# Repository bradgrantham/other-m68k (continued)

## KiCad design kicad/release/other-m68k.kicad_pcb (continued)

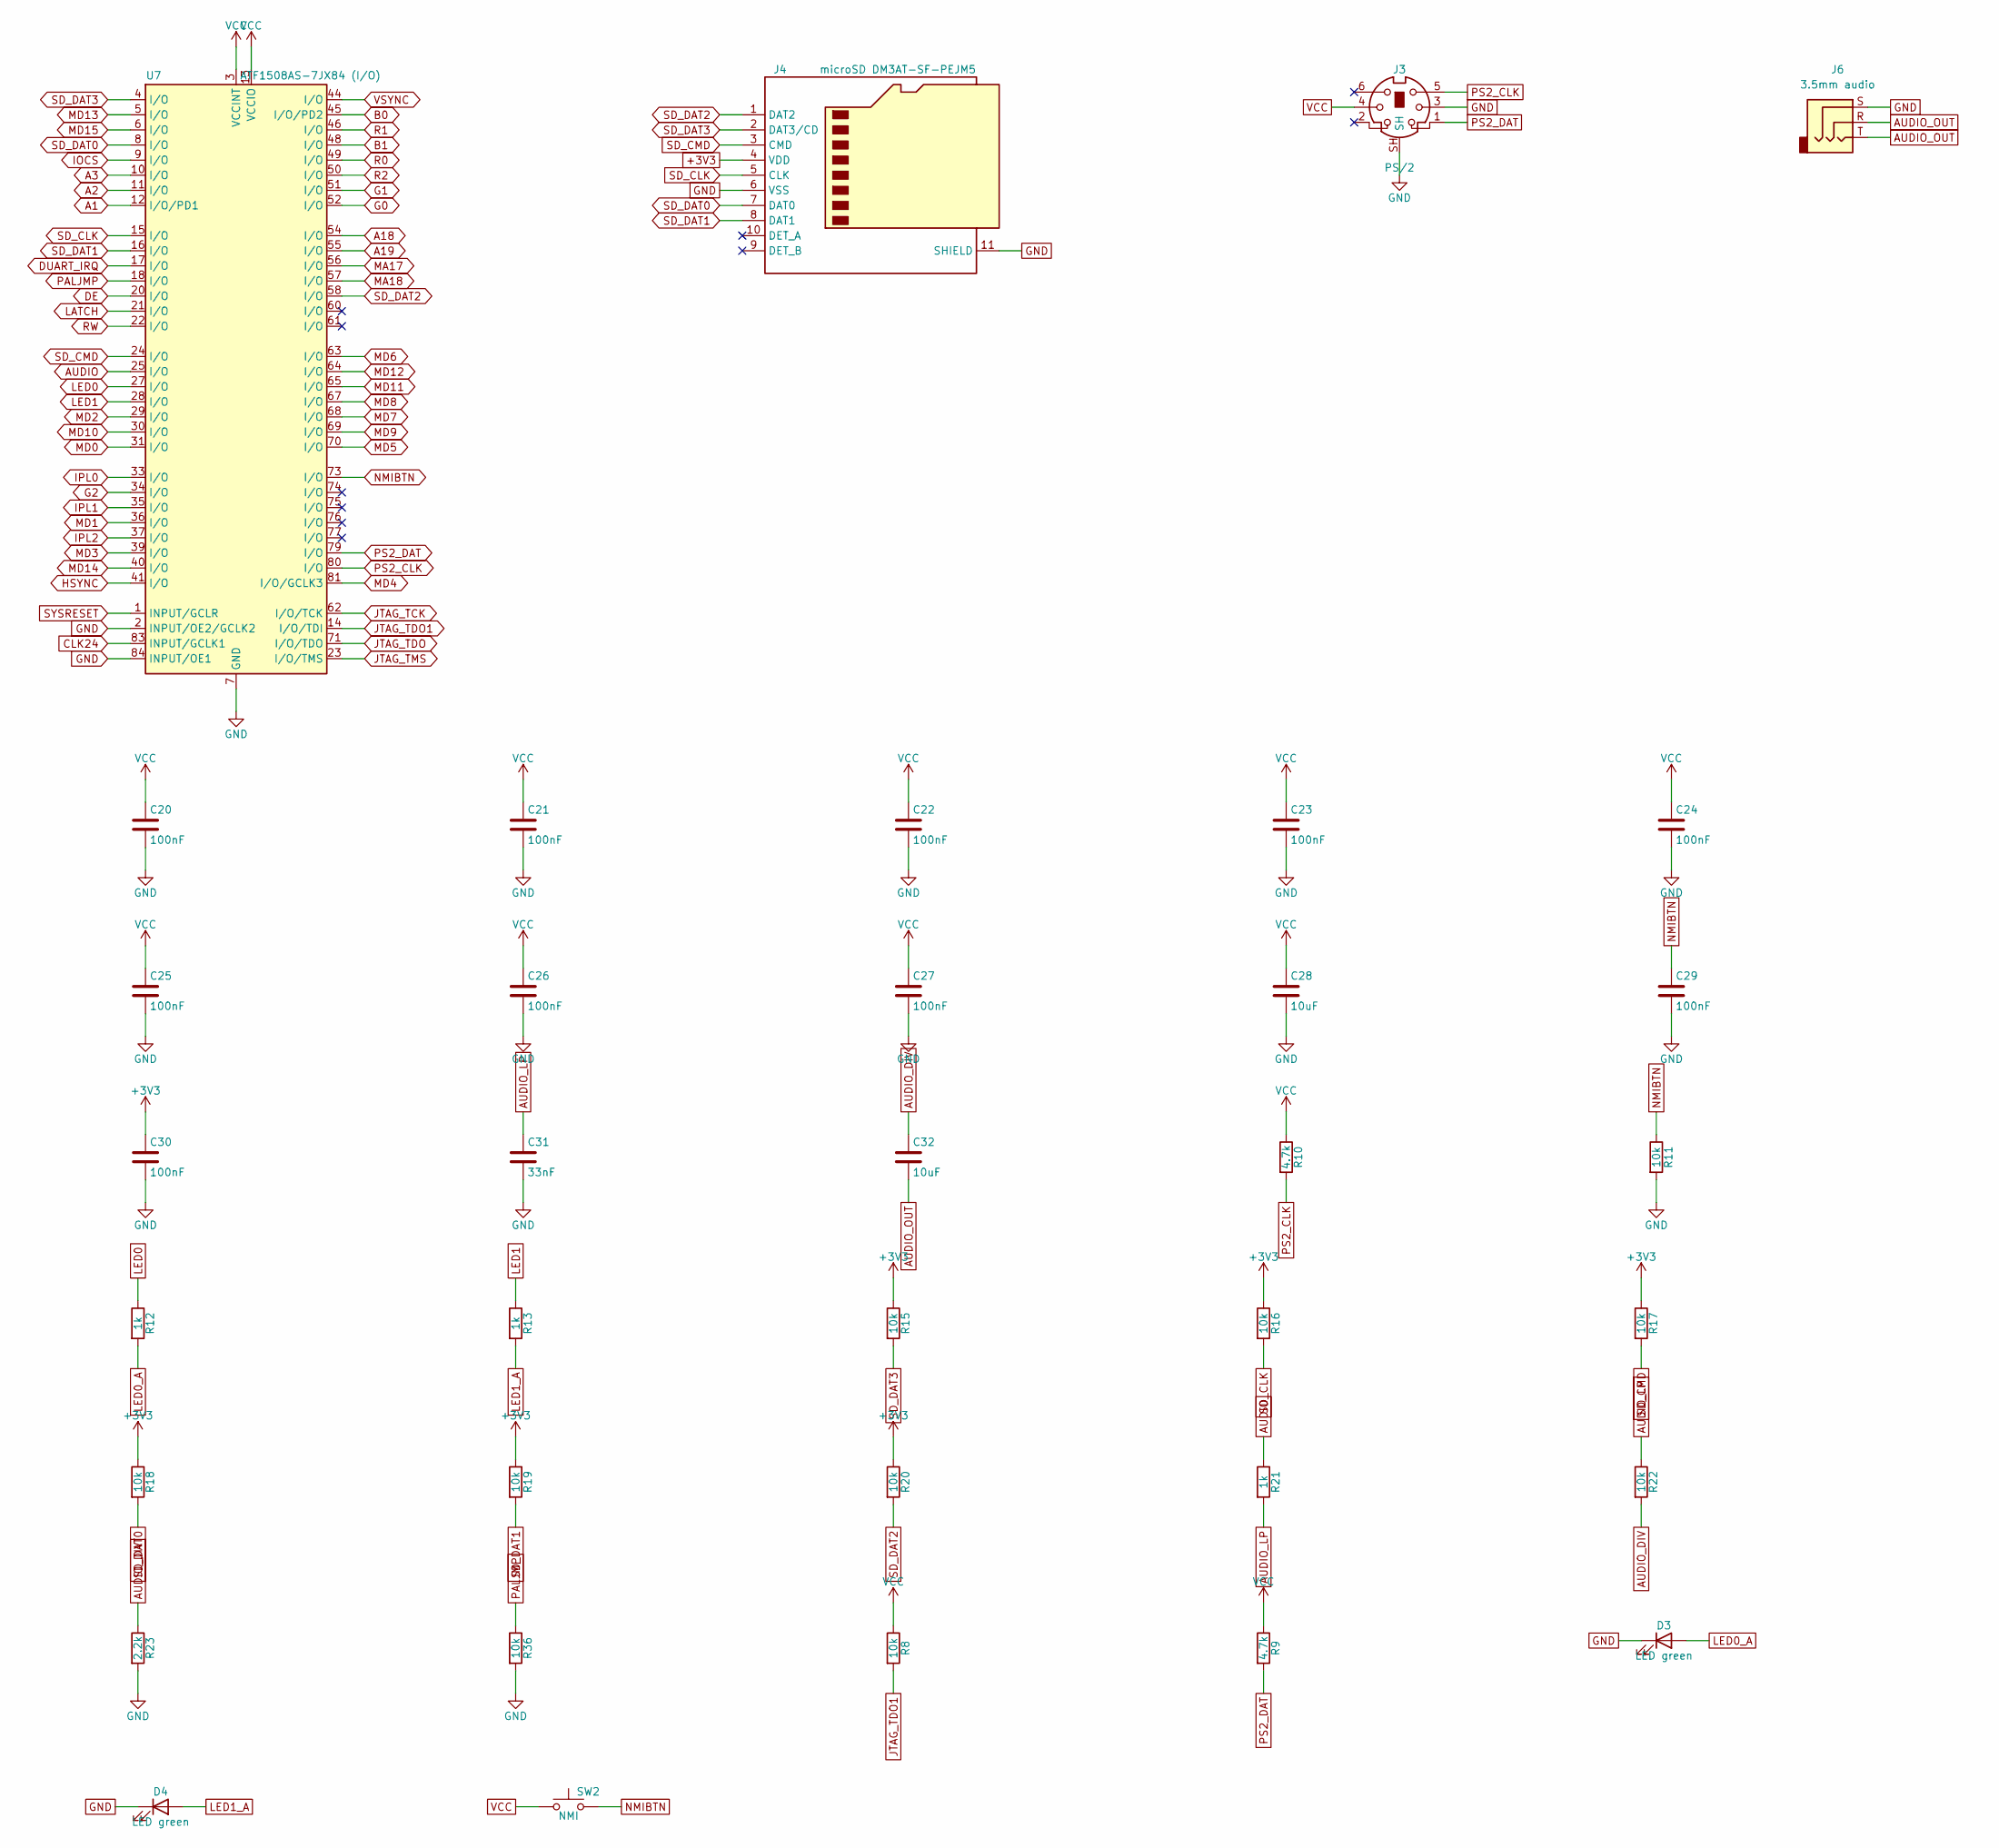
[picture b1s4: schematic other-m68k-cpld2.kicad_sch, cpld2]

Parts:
C20, C21, C22, C23, C24, C25, C26, C27, C29, C30: 100nF; C_0603_1608Metric; MPN CL10B104KB8NNNC; LCSC C1591
C28, C32: 10uF; C_0805_2012Metric; MPN CL21A106KAYNNNE; LCSC C15850
C31: 33nF; C_0603_1608Metric; MPN CL10B333KB8NFNC; LCSC C307488
D3, D4: LED green; LED_0805_2012Metric; MPN LTST-C171GKT
J3: PS/2; MiniDIN-6_CUI_MD-60SM_Horizontal; MPN MD-60SM
J4: microSD DM3AT-SF-PEJM5; microSD_HC_Hirose_DM3AT-SF-PEJM5; MPN DM3AT-SF-PEJM5
J6: 3.5mm audio; Jack_3.5mm_CUI_SJ1-3523N_Horizontal; MPN SJ1-3523N
R8, R11, R15, R16, R17, R18, R19, R20, R22, R36: 10k; R_0603_1608Metric; MPN RC0603FR-0710KL; LCSC C25804
R9, R10: 4.7k; R_0603_1608Metric; MPN RC0603FR-074K7L; LCSC C23162
R12, R13, R21: 1k; R_0603_1608Metric; MPN RC0603FR-071KL; LCSC C21190
R23: 2.2k; R_0603_1608Metric; MPN RC0603FR-072K2L; LCSC C4190
SW2: NMI; SW_PUSH_6mm; MPN B3F-1000
U7: ATF1508AS-7JX84 (I/O); PLCC-84_THT-Socket; MPN ATF1508AS-7JX84

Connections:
+3V3: C30.1, J4.4 (VDD), R15.1, R16.1, R17.1, R18.1, R19.1, R20.1; also elsewhere on the board
A1: U7.12 (I/O/PD1); also elsewhere on the board
A2: U7.11 (I/O); also elsewhere on the board
A3: U7.10 (I/O); also elsewhere on the board
A18: U7.54 (I/O); also elsewhere on the board
A19: U7.55 (I/O); also elsewhere on the board
AUDIO: R21.1, U7.25 (I/O)
AUDIO_DIV: C32.1, R22.2, R23.1
AUDIO_LP: C31.1, R21.2, R22.1
AUDIO_OUT: C32.2, J6.R, J6.T
B0: U7.45 (I/O/PD2); also elsewhere on the board
B1: U7.48 (I/O); also elsewhere on the board
CLK24: U7.83 (INPUT/GCLK1); also elsewhere on the board
DE: U7.20 (I/O); also elsewhere on the board
DUART_IRQ: U7.17 (I/O); also elsewhere on the board
G0: U7.52 (I/O); also elsewhere on the board
G1: U7.51 (I/O); also elsewhere on the board
G2: U7.34 (I/O); also elsewhere on the board
GND: C20.2, C21.2, C22.2, C23.2, C24.2, C25.2, C26.2, C27.2, C28.2, C29.2, C30.2, C31.2, D3.1 (K), D4.1 (K), J3.3, J3.SH, J4.6 (VSS), J4.11 (SHIELD), J6.S, R11.2, R23.2, R36.2, U7.2 (INPUT/OE2/GCLK2), U7.7 (GND), U7.19 (GND), U7.32 (GND), U7.42 (GND), U7.47 (GND), U7.59 (GND), U7.72 (GND), U7.82 (GND), U7.84 (INPUT/OE1); also elsewhere on the board
HSYNC: U7.41 (I/O); also elsewhere on the board
IOCS: U7.9 (I/O); also elsewhere on the board
IPL0: U7.33 (I/O); also elsewhere on the board
IPL1: U7.35 (I/O); also elsewhere on the board
IPL2: U7.37 (I/O); also elsewhere on the board
JTAG_TCK: U7.62 (I/O/TCK); also elsewhere on the board
JTAG_TDO: U7.71 (I/O/TDO); also elsewhere on the board
JTAG_TDO1: R8.2, U7.14 (I/O/TDI); also elsewhere on the board
JTAG_TMS: U7.23 (I/O/TMS); also elsewhere on the board
LATCH: U7.21 (I/O); also elsewhere on the board
LED0: R12.1, U7.27 (I/O)
LED0_A: D3.2 (A), R12.2
LED1: R13.1, U7.28 (I/O)
LED1_A: D4.2 (A), R13.2
MA17: U7.56 (I/O); also elsewhere on the board
MA18: U7.57 (I/O); also elsewhere on the board
MD0: U7.31 (I/O); also elsewhere on the board
MD1: U7.36 (I/O); also elsewhere on the board
MD2: U7.29 (I/O); also elsewhere on the board
MD3: U7.39 (I/O); also elsewhere on the board
MD4: U7.81 (I/O/GCLK3); also elsewhere on the board
MD5: U7.70 (I/O); also elsewhere on the board
MD6: U7.63 (I/O); also elsewhere on the board
MD7: U7.68 (I/O); also elsewhere on the board
MD8: U7.67 (I/O); also elsewhere on the board
MD9: U7.69 (I/O); also elsewhere on the board
MD10: U7.30 (I/O); also elsewhere on the board
MD11: U7.65 (I/O); also elsewhere on the board
MD12: U7.64 (I/O); also elsewhere on the board
MD13: U7.5 (I/O); also elsewhere on the board
MD14: U7.40 (I/O); also elsewhere on the board
MD15: U7.6 (I/O); also elsewhere on the board
NMIBTN: C29.1, R11.1, SW2.2, U7.73 (I/O)
PALJMP: R36.1, U7.18 (I/O)
PS2_CLK: J3.5, R10.2, U7.80 (I/O)
PS2_DAT: J3.1, R9.2, U7.79 (I/O)
R0: U7.49 (I/O); also elsewhere on the board
R1: U7.46 (I/O); also elsewhere on the board
R2: U7.50 (I/O); also elsewhere on the board
RW: U7.22 (I/O); also elsewhere on the board
SD_CLK: J4.5 (CLK), R16.2, U7.15 (I/O)
SD_CMD: J4.3 (CMD), R17.2, U7.24 (I/O)
SD_DAT0: J4.7 (DAT0), R18.2, U7.8 (I/O)
SD_DAT1: J4.8 (DAT1), R19.2, U7.16 (I/O)
SD_DAT2: J4.1 (DAT2), R20.2, U7.58 (I/O)
SD_DAT3: J4.2 (DAT3/CD), R15.2, U7.4 (I/O)
SYSRESET: U7.1 (INPUT/GCLR); also elsewhere on the board
VCC: C20.1, C21.1, C22.1, C23.1, C24.1, C25.1, C26.1, C27.1, C28.1, J3.4, R8.1, R9.1, R10.1, SW2.1, U7.3 (VCCINT), U7.13 (VCCIO), U7.26 (VCCIO), U7.38 (VCCIO), U7.43 (VCCINT), U7.53 (VCCIO), U7.66 (VCCIO), U7.78 (VCCIO); also elsewhere on the board
VSYNC: U7.44 (I/O); also elsewhere on the board

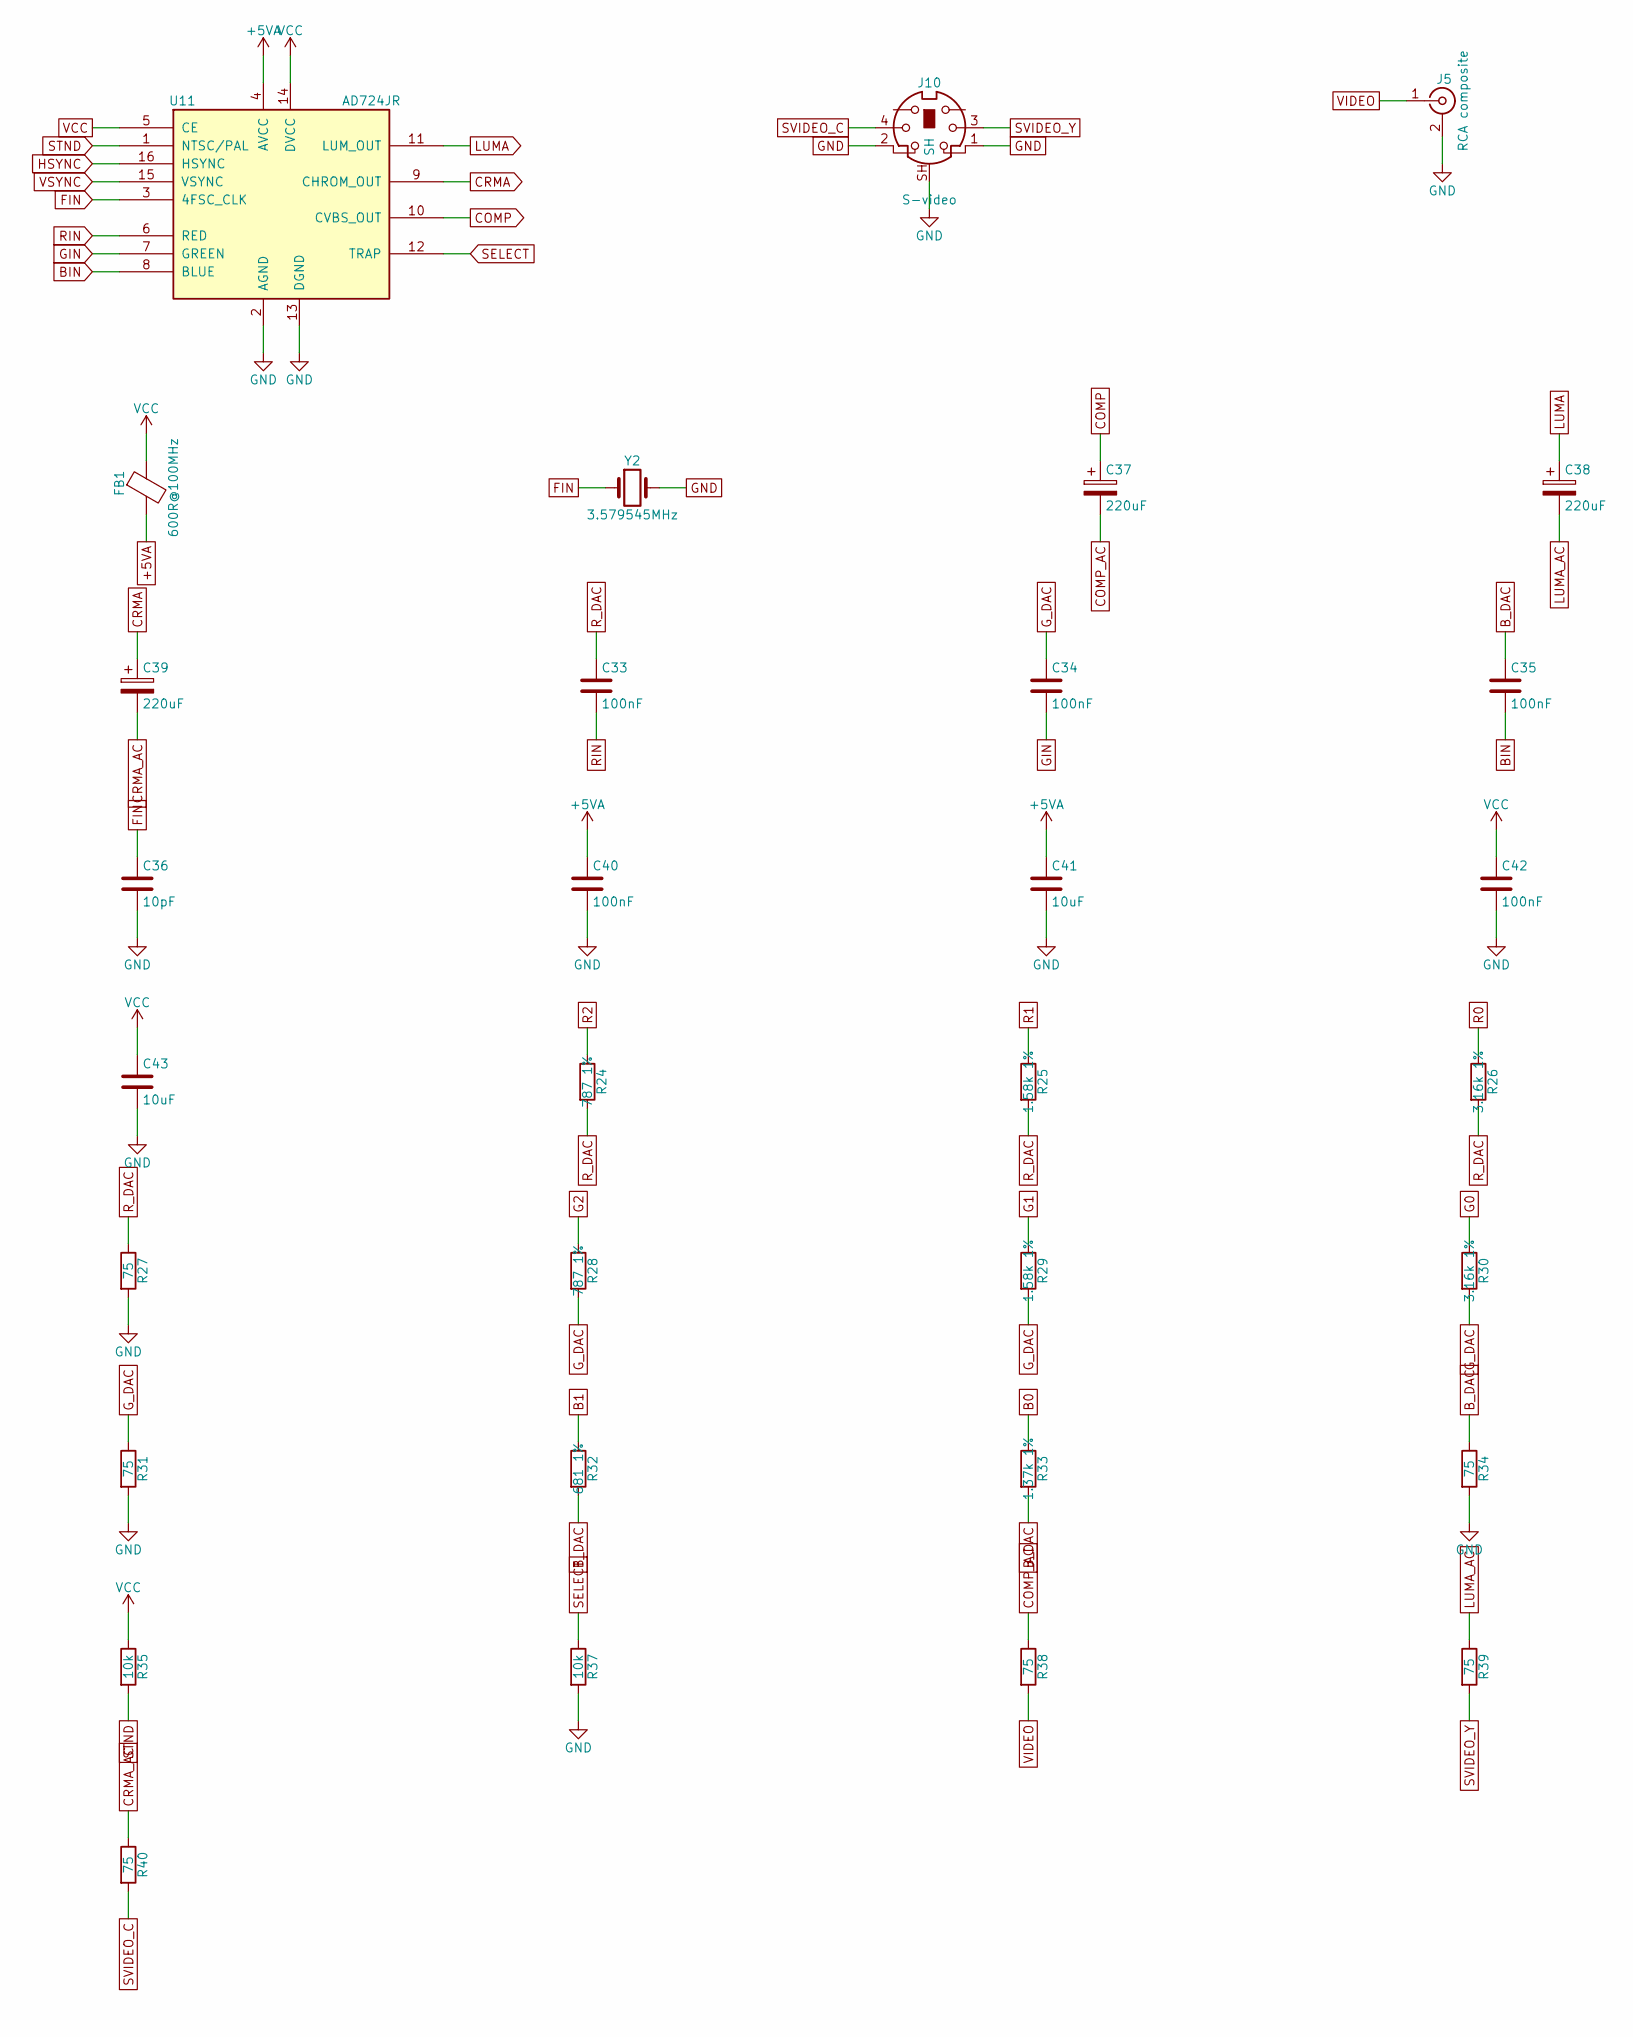
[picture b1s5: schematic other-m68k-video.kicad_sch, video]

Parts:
C33, C34, C35, C40, C42: 100nF; C_0603_1608Metric; MPN CL10B104KB8NNNC; LCSC C1591
C36: 10pF; C_0603_1608Metric; MPN CL10C100JB8NNNC; LCSC C32949
C37, C38, C39: 220uF; CP_Radial_D6.3mm_P2.50mm; MPN 16ZLH220MEFC6.3X11
C41, C43: 10uF; C_0805_2012Metric; MPN CL21A106KAYNNNE; LCSC C15850
FB1: 600R@100MHz; L_0603_1608Metric; MPN BLM18PG601SN1D
J5: RCA composite; RCA_CUI_RCJ-041_Horizontal; MPN RCJ-041
J10: S-video; MiniDIN-4_CUI_MD-40SM_Horizontal; MPN MD-40SM
R24, R28: 787 1%; R_0603_1608Metric; MPN RC0603FR-07787RL
R25, R29: 1.58k 1%; R_0603_1608Metric; MPN RC0603FR-071K58L
R26, R30: 3.16k 1%; R_0603_1608Metric; MPN RC0603FR-073K16L
R27, R31, R34, R38, R39, R40: 75; R_0603_1608Metric; MPN RC0603FR-0775RL
R32: 681 1%; R_0603_1608Metric; MPN RC0603FR-07681RL
R33: 1.37k 1%; R_0603_1608Metric; MPN RC0603FR-071K37L
R35, R37: 10k; R_0603_1608Metric; MPN RC0603FR-0710KL; LCSC C25804
U11: AD724JR; SOIC-16W_7.5x10.3mm_P1.27mm; MPN AD724JRZ
Y2: 3.579545MHz; Crystal_HC49-U_Vertical; MPN ECS-35-17-4X

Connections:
+5VA: C40.1, C41.1, FB1.2, U11.4 (AVCC)
B0: R33.1; also elsewhere on the board
B1: R32.1; also elsewhere on the board
BIN: C35.2, U11.8 (BLUE)
B_DAC: C35.1, R32.2, R33.2, R34.1
COMP: C37.1, U11.10 (CVBS_OUT)
COMP_AC: C37.2, R38.1
CRMA: C39.1, U11.9 (CHROM_OUT)
CRMA_AC: C39.2, R40.1
FIN: C36.1, U11.3 (4FSC_CLK), Y2.1
G0: R30.1; also elsewhere on the board
G1: R29.1; also elsewhere on the board
G2: R28.1; also elsewhere on the board
GIN: C34.2, U11.7 (GREEN)
GND: C36.2, C40.2, C41.2, C42.2, C43.2, J5.2 (Ext), J10.1, J10.2, J10.SH, R27.2, R31.2, R34.2, R37.2, U11.2 (AGND), U11.13 (DGND), Y2.2; also elsewhere on the board
G_DAC: C34.1, R28.2, R29.2, R30.2, R31.1
HSYNC: U11.16 (HSYNC); also elsewhere on the board
LUMA: C38.1, U11.11 (LUM_OUT)
LUMA_AC: C38.2, R39.1
R0: R26.1; also elsewhere on the board
R1: R25.1; also elsewhere on the board
R2: R24.1; also elsewhere on the board
RIN: C33.2, U11.6 (RED)
R_DAC: C33.1, R24.2, R25.2, R26.2, R27.1
SELECT: R37.1, U11.12 (TRAP)
STND: R35.2, U11.1 (NTSC/PAL)
SVIDEO_C: J10.4, R40.2
SVIDEO_Y: J10.3, R39.2
VCC: C42.1, C43.1, FB1.1, R35.1, U11.5 (CE), U11.14 (DVCC); also elsewhere on the board
VIDEO: J5.1 (In), R38.2; also elsewhere on the board
VSYNC: U11.15 (VSYNC); also elsewhere on the board

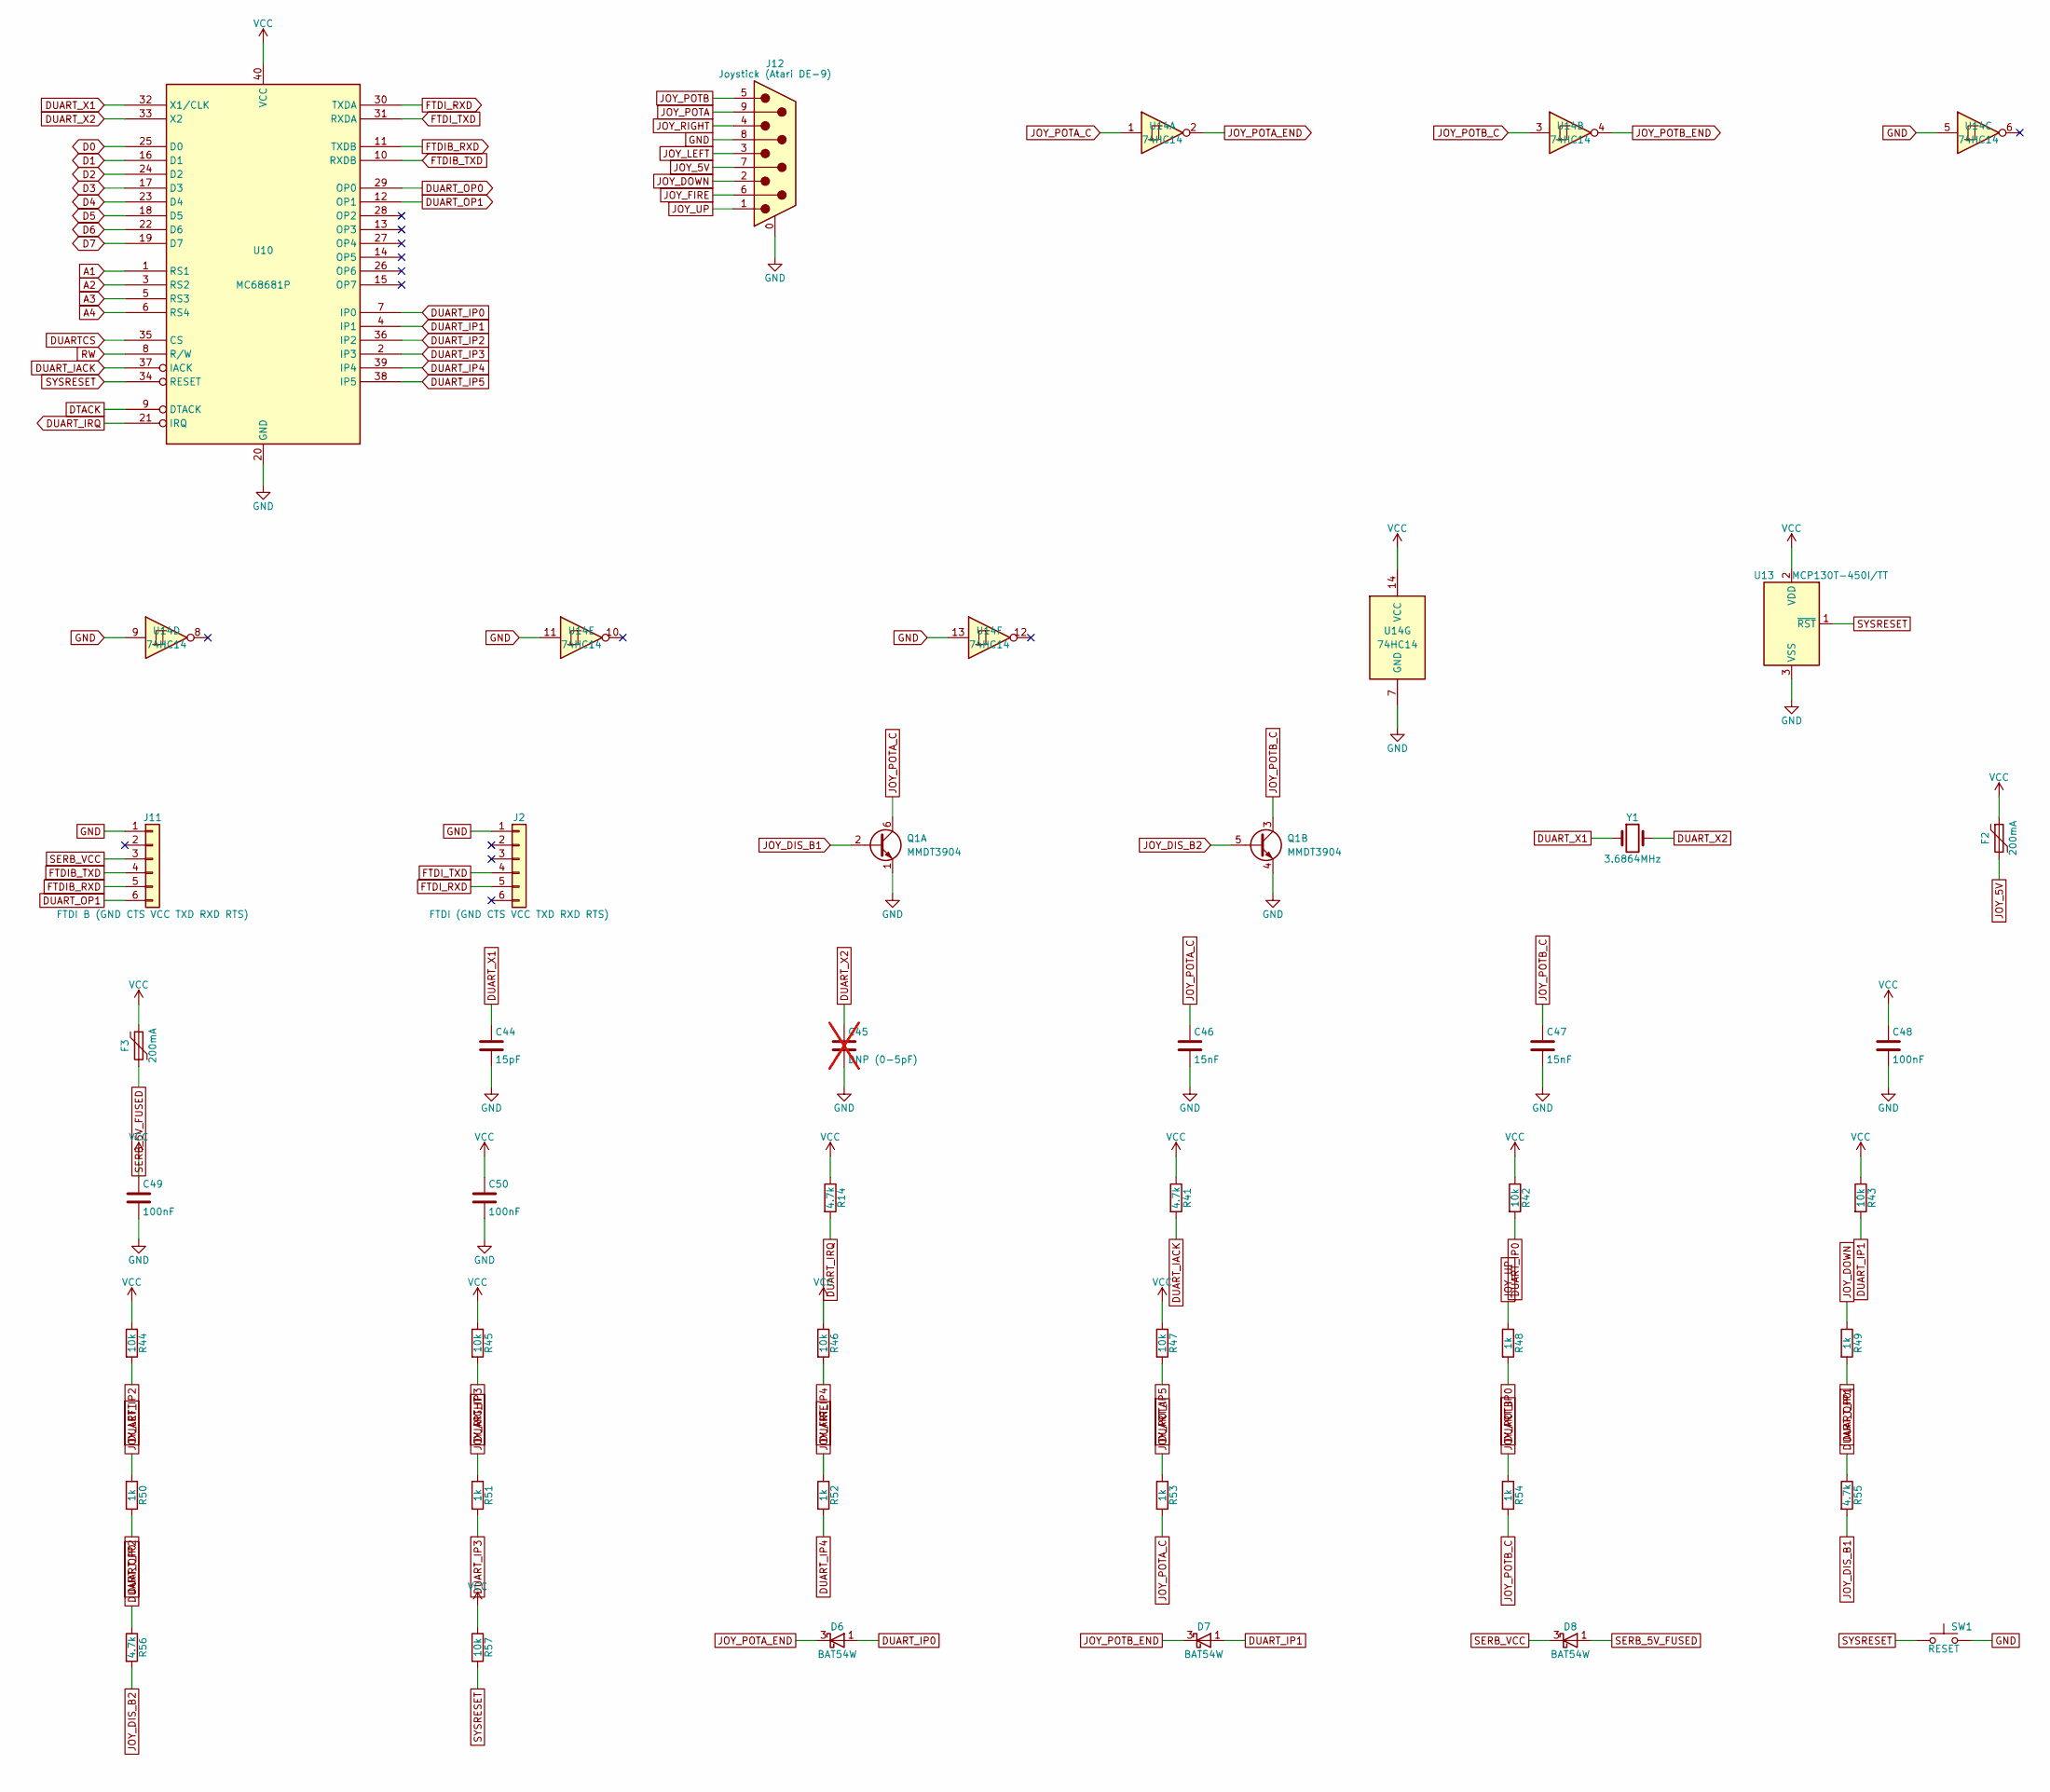
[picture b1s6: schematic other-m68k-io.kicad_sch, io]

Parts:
C44: 15pF; C_0603_1608Metric; MPN CL10C150JB8NNNC; LCSC C1644
C45: DNP (0-5pF); C_0603_1608Metric; not fitted
C46, C47: 15nF; C_0603_1608Metric; MPN CL10B153KB8NNNC
C48, C49, C50: 100nF; C_0603_1608Metric; MPN CL10B104KB8NNNC; LCSC C1591
D6, D7, D8: BAT54W; SOT-323_SC-70; MPN BAT54W,115; LCSC C8657
F2, F3: 200mA; Fuse_1206_3216Metric; MPN 1206L020YR
J2: FTDI (GND CTS VCC TXD RXD RTS); PinHeader_1x06_P2.54mm_Vertical; MPN PRPC006SAAN-RC
J11: FTDI B (GND CTS VCC TXD RXD RTS); PinHeader_1x06_P2.54mm_Vertical; MPN PRPC006SAAN-RC
J12: Joystick (Atari DE-9); DSUB-9_Pins_Horizontal_P2.77x2.84mm_EdgePinOffset7.70mm_Hou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; MPN L717SDE09PA4CH4F
Q1: MMDT3904; SOT-363_SC-70-6; MPN MMDT3904-7-F; LCSC C8706
R14, R41, R55, R56: 4.7k; R_0603_1608Metric; MPN RC0603FR-074K7L; LCSC C23162
R42, R43, R44, R45, R46, R47, R57: 10k; R_0603_1608Metric; MPN RC0603FR-0710KL; LCSC C25804
R48, R49, R50, R51, R52, R53, R54: 1k; R_0603_1608Metric; MPN RC0603FR-071KL; LCSC C21190
SW1: RESET; SW_PUSH_6mm; MPN B3F-1000
U10: MC68681P; DIP-40_W15.24mm_Socket; MPN MC68681P
U13: MCP130T-450I/TT; SOT-23; MPN MCP130T-450I/TT
U14: 74HC14; SOIC-14_3.9x8.7mm_P1.27mm; MPN 74HC14D,653; LCSC C5612
Y1: 3.6864MHz; Crystal_HC49-U_Vertical; MPN ECS-36-20-4XDN

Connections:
A1: U10.1 (RS1); also elsewhere on the board
A2: U10.3 (RS2); also elsewhere on the board
A3: U10.5 (RS3); also elsewhere on the board
A4: U10.6 (RS4); also elsewhere on the board
D0: U10.25 (D0); also elsewhere on the board
D1: U10.16 (D1); also elsewhere on the board
D2: U10.24 (D2); also elsewhere on the board
D3: U10.17 (D3); also elsewhere on the board
D4: U10.23 (D4); also elsewhere on the board
D5: U10.18 (D5); also elsewhere on the board
D6: U10.22 (D6); also elsewhere on the board
D7: U10.19 (D7); also elsewhere on the board
DTACK: U10.9 (DTACK); also elsewhere on the board
DUARTCS: U10.35 (CS); also elsewhere on the board
DUART_IACK: R41.2, U10.37 (IACK)
DUART_IP0: D6.1 (A), R42.2, R48.2, U10.7 (IP0)
DUART_IP1: D7.1 (A), R43.2, R49.2, U10.4 (IP1)
DUART_IP2: R44.2, R50.2, U10.36 (IP2)
DUART_IP3: R45.2, R51.2, U10.2 (IP3)
DUART_IP4: R46.2, R52.2, U10.39 (IP4)
DUART_IP5: R47.2, U10.38 (IP5)
DUART_IRQ: R14.2, U10.21 (IRQ); also elsewhere on the board
DUART_OP0: R55.1, R56.1, U10.29 (OP0)
DUART_OP1: J11.6, U10.12 (OP1)
DUART_X1: C44.1, U10.32 (X1/CLK), Y1.1
DUART_X2: C45.1, U10.33 (X2), Y1.2
FTDIB_RXD: J11.5, U10.11 (TXDB)
FTDIB_TXD: J11.4, U10.10 (RXDB)
FTDI_RXD: J2.5, U10.30 (TXDA)
FTDI_TXD: J2.4, U10.31 (RXDA)
GND: C44.2, C45.2, C46.2, C47.2, C48.2, C49.2, C50.2, J2.1, J11.1, J12.0 (PAD), J12.8, Q1.1 (E1), Q1.4 (E2), SW1.2, U10.20 (GND), U13.3 (VSS), U14.5, U14.7 (GND), U14.9, U14.11, U14.13; also elsewhere on the board
JOY_5V: F2.2, J12.7
JOY_DIS_B1: Q1.2 (B1), R55.2
JOY_DIS_B2: Q1.5 (B2), R56.2
JOY_DOWN: J12.2, R49.1
JOY_FIRE: J12.6, R52.1
JOY_LEFT: J12.3, R50.1
JOY_POTA: J12.9, R53.1
JOY_POTA_C: C46.1, Q1.6 (C1), R53.2, U14.1
JOY_POTA_END: D6.3 (K), U14.2
JOY_POTB: J12.5, R54.1
JOY_POTB_C: C47.1, Q1.3 (C2), R54.2, U14.3
JOY_POTB_END: D7.3 (K), U14.4
JOY_RIGHT: J12.4, R51.1
JOY_UP: J12.1, R48.1
RW: U10.8 (R/W); also elsewhere on the board
SERB_5V_FUSED: D8.1 (A), F3.2
SERB_VCC: D8.3 (K), J11.3
SYSRESET: R57.2, SW1.1, U10.34 (RESET), U13.1 (~RST); also elsewhere on the board
VCC: C48.1, C49.1, C50.1, F2.1, F3.1, R14.1, R41.1, R42.1, R43.1, R44.1, R45.1, R46.1, R47.1, R57.1, U10.40 (VCC), U13.2 (VDD), U14.14 (VCC); also elsewhere on the board

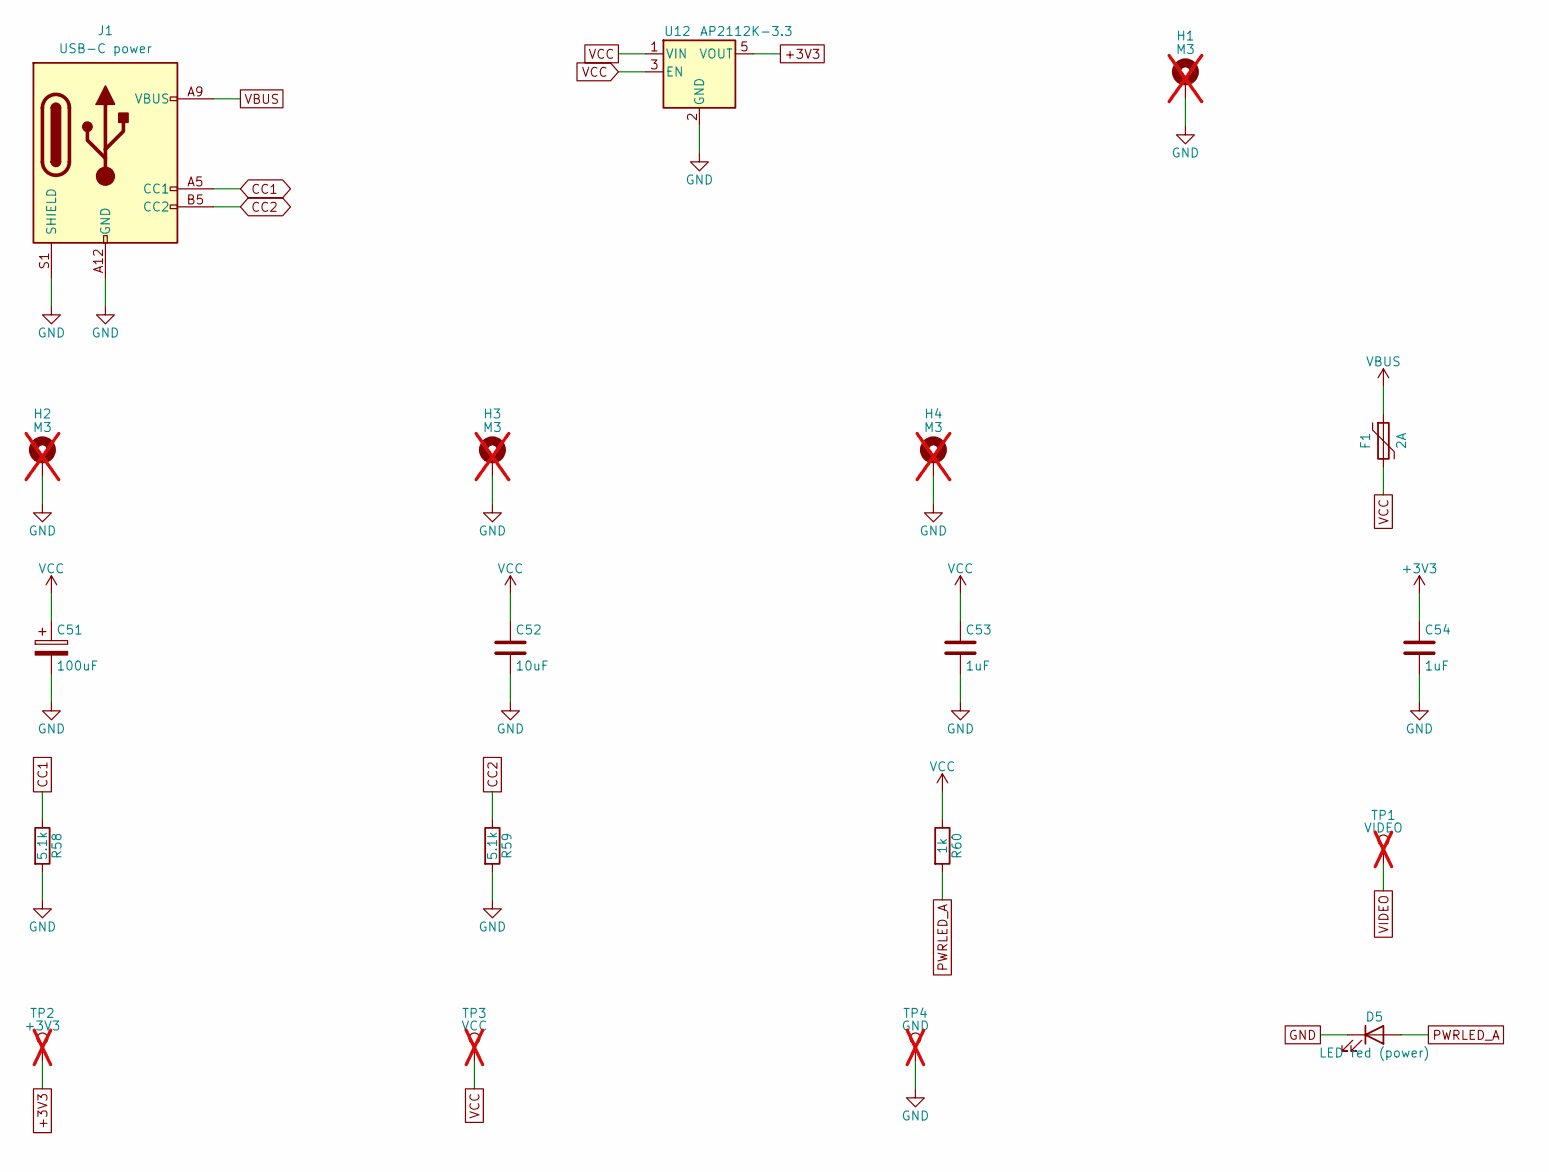
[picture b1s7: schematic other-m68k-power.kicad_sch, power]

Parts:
C51: 100uF; CP_Radial_D6.3mm_P2.50mm; MPN 35ZLH100MEFC6.3X11
C52: 10uF; C_0805_2012Metric; MPN CL21A106KAYNNNE; LCSC C15850
C53, C54: 1uF; C_0603_1608Metric; MPN CL10A105KB8NNNC; LCSC C15849
D5: LED red (power); LED_0805_2012Metric; MPN LTST-C171KRKT
F1: 2A; Fuse_1206_3216Metric; MPN 1206L200PR
H1, H2, H3, H4: M3; MountingHole_3.2mm_M3_Pad; not fitted
J1: USB-C power; USB_C_Receptacle_GCT_USB4125-xx-x_6P_TopMnt_Horizontal; MPN USB4125-GF-A-0190
R58, R59: 5.1k; R_0603_1608Metric; MPN RC0603FR-075K1L; LCSC C23186
R60: 1k; R_0603_1608Metric; MPN RC0603FR-071KL; LCSC C21190
TP1: VIDEO; TestPoint_Pad_D1.5mm; not fitted
TP2: +3V3; TestPoint_Pad_D1.5mm; not fitted
TP3: VCC; TestPoint_Pad_D1.5mm; not fitted
TP4: GND; TestPoint_Pad_D1.5mm; not fitted
U12: AP2112K-3.3; SOT-23-5; MPN AP2112K-3.3TRG1; LCSC C51118

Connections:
+3V3: C54.1, TP2.1, U12.5 (VOUT); also elsewhere on the board
CC1: J1.A5 (CC1), R58.1
CC2: J1.B5 (CC2), R59.1
GND: C51.2, C52.2, C53.2, C54.2, D5.1 (K), H1.1, H2.1, H3.1, H4.1, J1.A12 (GND), J1.B12 (GND), J1.S1 (SHIELD), R58.2, R59.2, TP4.1, U12.2 (GND); also elsewhere on the board
PWRLED_A: D5.2 (A), R60.2
VBUS: F1.1, J1.A9 (VBUS), J1.B9 (VBUS)
VCC: C51.1, C52.1, C53.1, F1.2, R60.1, TP3.1, U12.1 (VIN), U12.3 (EN); also elsewhere on the board
VIDEO: TP1.1; also elsewhere on the board

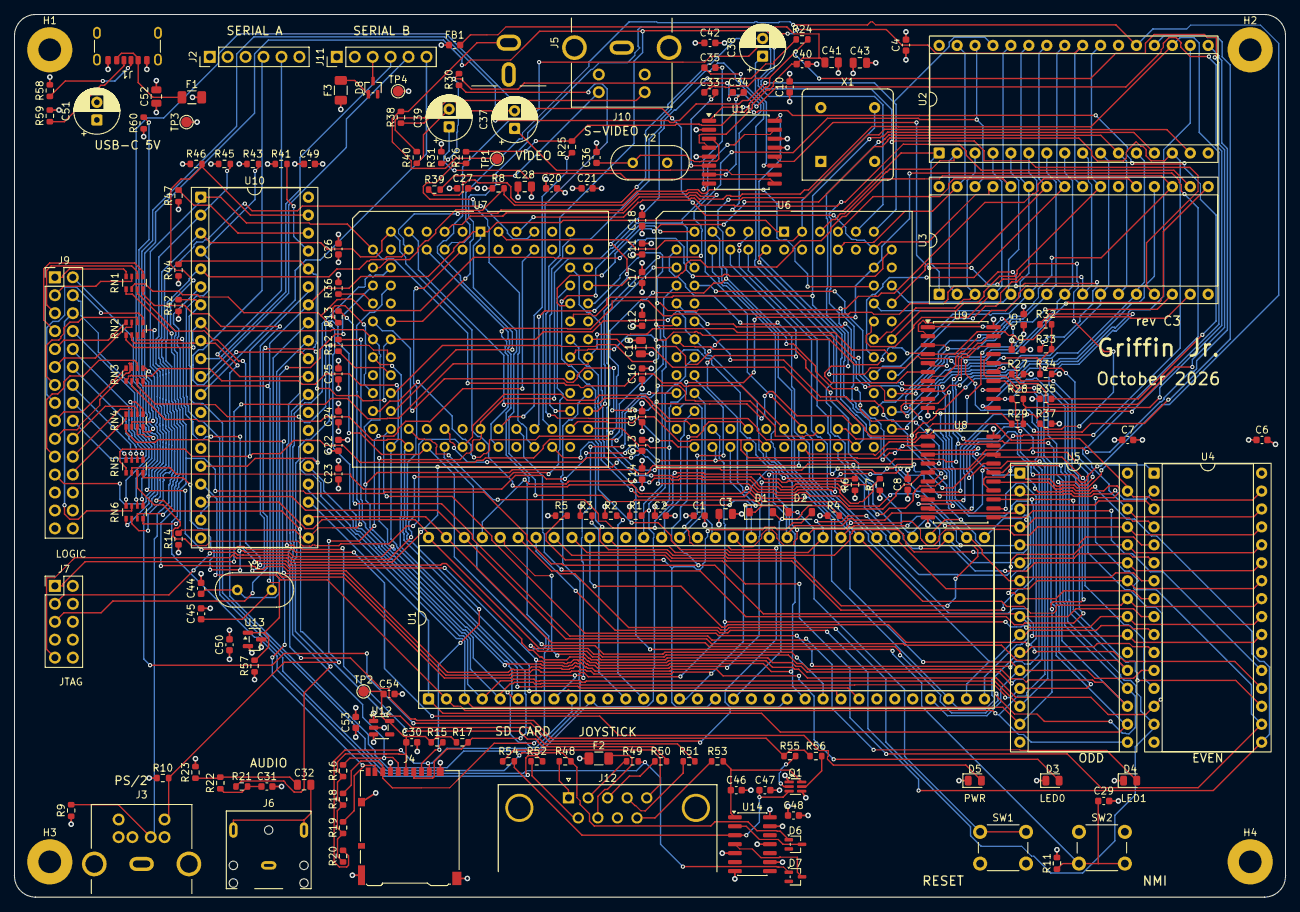
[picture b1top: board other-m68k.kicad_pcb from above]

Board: 4 copper layers, 180.0 x 125.0 mm, 171 parts (0 on the bottom side), 216 nets.
